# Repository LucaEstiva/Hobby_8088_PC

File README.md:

# Hobby_8088_PC
Studio e progetti di un PC basato su processore Intel 8088

> E' un progetto realizzato nel tempo libero, quindi ancora incompleto, ma, viste le risorse disponibili, sicuramente funzionante.
> D'altro canto sarebbe sufficiente "copiare" dagli schemi forniti l'intera circuiteria ed assemblare cosi il PC. Tuttavia lo scopo
> del progetto è quello di capire l'architettura del PC XT IBM e, divertirsi con la logica dell'architettura, aggiornarla, oppure volendo,
> modificarla a piacere.

## Fonti:
-  https://it.wikipedia.org/wiki/IBM_Personal_Computer_XT
-  https://www.vlsisystemdesign.com/propagation-delay-of-cmos-inverter/

## Riferimenti:
-  https://www.youtube.com/@breadboardinglabs
-  https://www.youtube.com/@BenEater
-  https://www.youtube.com/@SladorSoft
-  https://www.youtube.com/@elijahmmiller
-  https://www.youtube.com/@alexthelion335
-  https://www.youtube.com/@JohnsBasement
-  https://www.youtube.com/@elijahmmiller
-  ---
-  https://www.youtube.com/@adriansdigitalbasement
-  https://www.youtube.com/@PsychogenicTechnologies
-  https://www.youtube.com/@DrMattRegan
-  https://www.youtube.com/@KludgesFromKevinsCave
-  https://www.youtube.com/@nesoacademy
-  ---

-  https://www.zimmers.net/
-  https://github.com/skiselev
-  https://www.malinov.com/sergeys-projects/

-  ---
- [Digikey FPGA](https://www.youtube.com/watch?v=lLg1AgA2Xoo&list=PLEBQazB0HUyT1WmMONxRZn9NmQ_9CIKhb&ab_channel=DigiKey)
- https://www.minuszerodegrees.net/

- https://archive.org/
- https://archive.org/details/practicaldesignu0000pell/page/n1/mode/2up

- https://www.electronics-tutorials.ws/oscillator/crystal.html
- ---
# e molti molti altri. Grazie !
  
## Software utili ( solo alcuni, lista non aggiornata... ):

- [Logicly](https://logic.ly/demo/)
- [Kicad](https://www.kicad.org/) - CAD Utilizzato per la realizzazione degli schemi elettrici ( e circuiti stampati )
- [Circuitverse Simulator](https://circuitverse.org/simulator) - Importare i file dalla cartella Simulatore_Logica

## Simulazioni
[Proteus 8](https://www.labcenter.com/free-trial/)

## OS
[OSDev.org](https://wiki.osdev.org/Expanded_Main_Page)

## Libri:

- [The 80x86 IBM PC and compatible computers. Volumes I & II, Assembly language, design, and interfacing](https://archive.org/details/80x86ibmpccompat0001mazi/page/n1/mode/2up)

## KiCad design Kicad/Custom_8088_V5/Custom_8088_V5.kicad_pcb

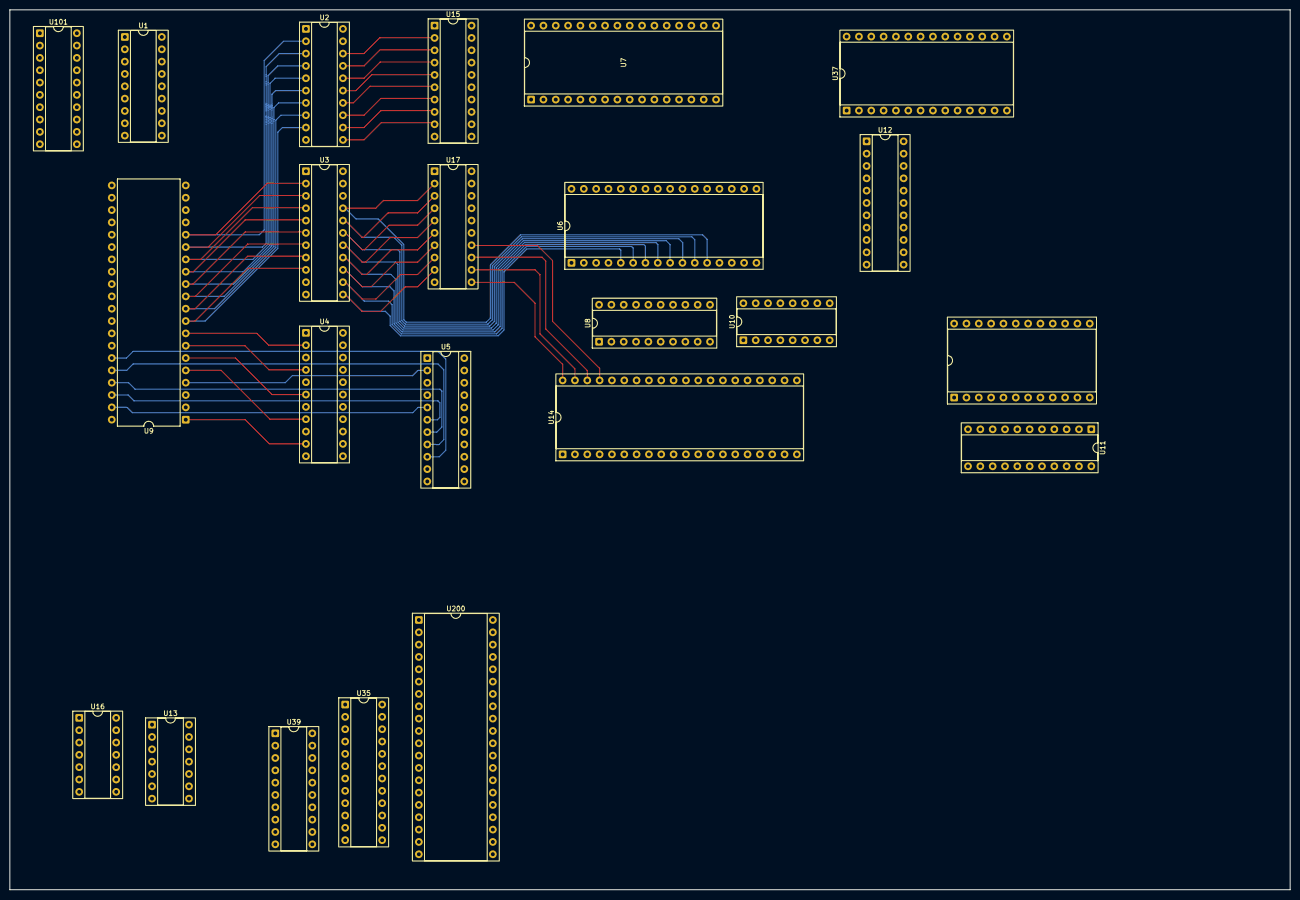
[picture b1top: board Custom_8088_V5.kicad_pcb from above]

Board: 2 copper layers, 263.8 x 181.2 mm, 23 parts (0 on the bottom side), 91 nets.

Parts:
U1: 82C84A; DIP-18_W7.62mm_Socket
U2, U15, U17, U39: 74AHCT245N; DIP-20_W7.62mm_Socket
U3, U5, U11: SN74AHCT573N; DIP-22_W7.62mm_Socket
U4, U12: SN72AHCT244N; DIP-22_W7.62mm_Socket
U6: HM628512C; DIP-32_W15.24mm_Socket
U7: AT29C010A-90PC; DIP-32_W15.24mm_Socket
U8: 8288; DIP-20_W7.62mm_Socket
U9: 8088_Max_Mode; DIP-40_W15.24mm
U10: 74HCT670; DIP-16_W7.62mm_Socket
U13: 74LS06N; DIP-14_W7.62mm_Socket
U14: 8237A; DIP-40_W15.24mm_Socket
U16: 74AHCT04; DIP-14_W7.62mm_Socket
U35: ATF22V10; DIP-24_W7.62mm_Socket
U37: 82C59A; DIP-28_W15.24mm_Socket
U38: TMP82C54P-2; DIP-24_W15.24mm_Socket
U101: ATF16V8C; DIP-20_W7.62mm_Socket
U200: VT82C42; DIP-40_W15.24mm_Socket

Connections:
+5V: U1.7 (~AEN2), U1.18 (Vcc), U2.20 (Vcc), U3.20 (Vcc), U4.20 (Vcc), U5.20 (Vcc), U6.32 (VCC), U7.32 (VCC), U8.20 (Vcc), U9.40 (VCC), U10.16 (Vcc), U11.20 (Vcc), U12.10 (GND), U12.20 (Vcc), U13.14 (VCC), U14.5 (PIN5), U14.31 (VCC), U15.20 (Vcc), U17.20 (Vcc), U37.28 (VCC), U38.24 (VCC), U101.20 (VCC), U200.40 (Vcc)
/A0: U3.19 (1Q), U6.12 (A0), U12.16 (1Y2), U17.2 (A1)
/A1: U3.18 (2Q), U6.11 (A1), U12.14 (1Y3), U17.3 (A2)
/A2: U3.17 (3Q), U6.10 (A2), U12.12 (1Y4), U17.4 (A3)
/A3: U3.16 (4Q), U6.9 (A3), U12.9 (2Y1), U17.5 (A4)
/A4: U3.15 (5Q), U6.8 (A4), U12.7 (2Y2), U17.6 (A5)
/A5: U3.14 (6Q), U6.7 (A5), U12.5 (2Y3), U17.7 (A6)
/A6: U3.13 (7Q), U6.6 (A6), U12.3 (2Y4), U17.8 (A7)
/A7: U3.12 (8Q), U6.5 (A7), U17.9 (A8)
/A8: U4.18 (1Y1), U6.27 (A8), U11.19 (1Q)
/A9: U4.16 (1Y2), U6.26 (A9), U11.18 (2Q)
/A10: U4.14 (1Y3), U6.23 (A10), U11.17 (3Q)
/A11: U4.12 (1Y4), U6.25 (A11), U11.16 (4Q)
/A12: U5.19 (1Q), U6.4 (A12), U11.15 (5Q)
/A13: U5.18 (2Q), U6.28 (A13), U11.14 (6Q)
/A14: U5.17 (3Q), U6.3 (A14), U11.13 (7Q)
/A15: U5.16 (4Q), U6.31 (A15), U11.12 (8Q)
/A16: U5.15 (5Q), U6.2 (A16), U10.10 (Q0)
/A17: U5.14 (6Q), U6.30 (A17), U10.9 (Q1)
/A18: U5.13 (7Q), U6.1 (A18), U10.7 (Q2)
/A19: U5.12 (8Q), U10.6 (Q3)
/AENBRD: U3.1 (~OE), U4.1 (1~OE), U5.1 (~OE), U8.6 (~AEN), U8.14 (~INTA), U15.19 (~OE), U37.27 (A0)
/ALE: U3.11 (LE), U5.11 (LE), U8.5 (ALE)
/CLK88: U1.8 (CLK), U8.2 (CLK), U9.19 (CLK), U101.2 (I1)
/D0: U2.18 (B1), U6.13 (I/O0), U15.2 (A1)
/D1: U2.17 (B2), U6.14 (I/O1), U15.3 (A2)
/D2: U2.16 (B3), U6.15 (I/O2), U15.4 (A3)
/D3: U2.15 (B4), U6.17 (I/O3), U15.5 (A4)
/D4: U2.14 (B5), U6.18 (I/O4), U15.6 (A5)
/D5: U2.13 (B6), U6.19 (I/O5), U15.7 (A6)
/D6: U2.12 (B7), U6.20 (I/O6), U15.8 (A7)
/D7: U2.11 (B8), U6.21 (I/O7), U15.9 (A8)
/DMA ENABLE: U10.11 (~RE), U11.1 (~OE), U12.2 (1A1), U12.18 (1Y1)
/DMACLK: U14.12 (CLK), U101.19 (I/O)
/INTR: U9.17 (NMI), U37.18 (IR0)
/NC: U8.9 (~MWTC), U8.11 (~IOWC), U8.17 (MCE/~PDEN), U9.32 (~RD), U9.34 (HIGH), U14.9 (AEN), U37.16 (~SP/~EN)
/XA0: U7.12 (A0), U10.14 (WA), U12.4 (1A2), U14.32 (A0), U17.18 (B1)
/XA1: U7.11 (A1), U10.13 (WB), U12.6 (1A3), U14.33 (A1), U17.17 (B2)
/XA2: U7.10 (A2), U12.8 (1A4), U14.34 (A2), U17.16 (B3)
/XA3: U7.9 (A3), U12.11 (2A1), U14.35 (A3), U17.15 (B4)
/XA4: U7.8 (A4), U12.13 (2A2), U14.37 (A4), U17.14 (B5)
/XA5: U7.7 (A5), U12.15 (2A3), U14.38 (A5), U17.13 (B6)
/XA6: U7.6 (A6), U12.17 (2A4), U14.39 (A6), U17.12 (B7)
/XA7: U7.5 (A7), U14.40 (A7), U17.11 (B8)
/XD0: U7.13 (I/O0), U10.15 (D0), U11.2 (1D), U14.30 (DB0), U15.18 (B1), U37.10 (D1), U38.8 (D0)
/XD1: U7.14 (I/O1), U10.1 (D1), U11.3 (2D), U14.29 (DB1), U15.17 (B2), U37.9 (D2), U38.7 (D1)
/XD2: U7.15 (I/O2), U10.2 (D2), U11.4 (3D), U14.28 (DB2), U15.16 (B3), U37.8 (D3), U38.4 (D2)
/XD3: U7.17 (I/O3), U10.3 (D3), U11.5 (4D), U14.27 (DB3), U15.15 (B4), U37.7 (D4), U38.5 (D3)
/XD4: U7.18 (I/O4), U11.6 (5D), U14.26 (DB4), U15.14 (B5), U37.6 (D5)
/XD5: U7.19 (I/O5), U11.7 (6D), U14.23 (DB5), U15.13 (B6), U37.5 (D6), U38.3 (D5)
/XD6: U7.20 (I/O6), U11.8 (7D), U14.22 (DB6), U15.12 (B7), U37.4 (D7), U38.2 (D6)
/XD7: U7.21 (I/O7), U11.9 (8D), U14.21 (DB7), U15.11 (B8), U37.3 (~RD), U38.1 (D7)
/~AEN: U8.15 (CEN), U17.1 (DIR)
/~DACK2: U10.4 (RB), U14.14 (DACK2)
/~DACK3: U10.5 (RA), U14.15 (DACK3)
/~MEMR: U6.24 (~OE), U7.24 (~OE), U8.7 (~MRDC)
/~MEMW: U6.29 (~WE), U7.31 (~WE), U8.8 (~AMWC)
/~XIOR: U14.1 (~IOR), U37.2 (~WR), U38.22 (~RD)
/~XIOW: U14.2 (~IOW), U37.1 (~CS), U38.23 (~WR)
GND: U1.1 (CSYNC), U1.6 (RDY2), U1.9 (GND), U1.13 (F/~C), U1.15 (~ASYNC), U2.10 (GND), U3.10 (GND), U4.10 (GND), U5.10 (GND), U6.16 (GND), U7.16 (GND), U8.1 (IOB), U8.10 (GND), U9.1 (GND), U9.20 (GND), U9.33 (MN/~MX), U10.8 (GND), U11.10 (GND), U13.7 (GND), U14.19 (DREQ0), U14.20 (VSS), U15.10 (GND), U17.10 (GND), U17.19 (~OE), U37.14 (GND), U38.12 (GND), U101.10 (GND), U101.11 (I9/~OE), U200.20 (GND)
unnamed: U1.2 (PCLK), U101.1 (I/CLK)
unnamed: U1.5 (READY), U9.22 (READY)
unnamed: U1.10 (RESET), U9.21 (RESET), U14.13 (RESET), U101.3 (I2)
unnamed: U2.2 (A1), U3.2 (1D), U9.16 (AD0)
unnamed: U2.3 (A2), U3.3 (2D), U9.15 (AD1)
unnamed: U2.4 (A3), U3.4 (3D), U9.14 (AD2)
unnamed: U2.5 (A4), U3.5 (4D), U9.13 (AD3)
unnamed: U2.6 (A5), U3.6 (5D), U9.12 (AD4)
unnamed: U2.7 (A6), U3.7 (6D), U9.11 (AD5)
unnamed: U2.8 (A7), U3.8 (7D), U9.10 (AD6)
unnamed: U2.9 (A8), U3.9 (8D), U9.9 (AD7)
unnamed: U2.1 (DIR), U8.4 (DT/~R)
unnamed: U2.19 (~OE), U16.2
unnamed: U4.2 (1A1), U9.8 (A8)
unnamed: U4.4 (1A2), U9.7 (A9)
unnamed: U4.6 (1A3), U9.6 (A10)
unnamed: U4.8 (1A4), U9.5 (A11)
unnamed: U5.2 (1D), U9.4 (A12)
unnamed: U5.3 (2D), U9.3 (A13)
unnamed: U5.4 (3D), U9.2 (A14)
unnamed: U5.5 (4D), U9.39 (A15)
unnamed: U5.6 (5D), U9.38 (A16/S3)
unnamed: U5.7 (6D), U9.37 (A17/S4)
unnamed: U5.8 (7D), U9.36 (A18/S5)
unnamed: U5.9 (8D), U9.35 (A19/S6)
unnamed: U8.16 (DEN), U16.1
unnamed: U8.19 (~S0), U9.26 (~S0)
unnamed: U8.3 (~S1), U9.27 (~S1)
unnamed: U8.18 (~S2), U9.28 (~S2)
unnamed: U11.11 (LE), U14.8 (ADSTB)
unnamed: U14.36 (~EOP), U16.3

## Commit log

2025-02-09 Create Documenti.md
    Documentazione di riferimento
2025-02-09 Create Librerie_Kicad
2025-03-06 Added ABEL
2025-03-06 Correction
2025-03-06 Correction to md
2025-03-06 Uodate
2025-03-07 Sync
2025-05-25 Update CPLD
